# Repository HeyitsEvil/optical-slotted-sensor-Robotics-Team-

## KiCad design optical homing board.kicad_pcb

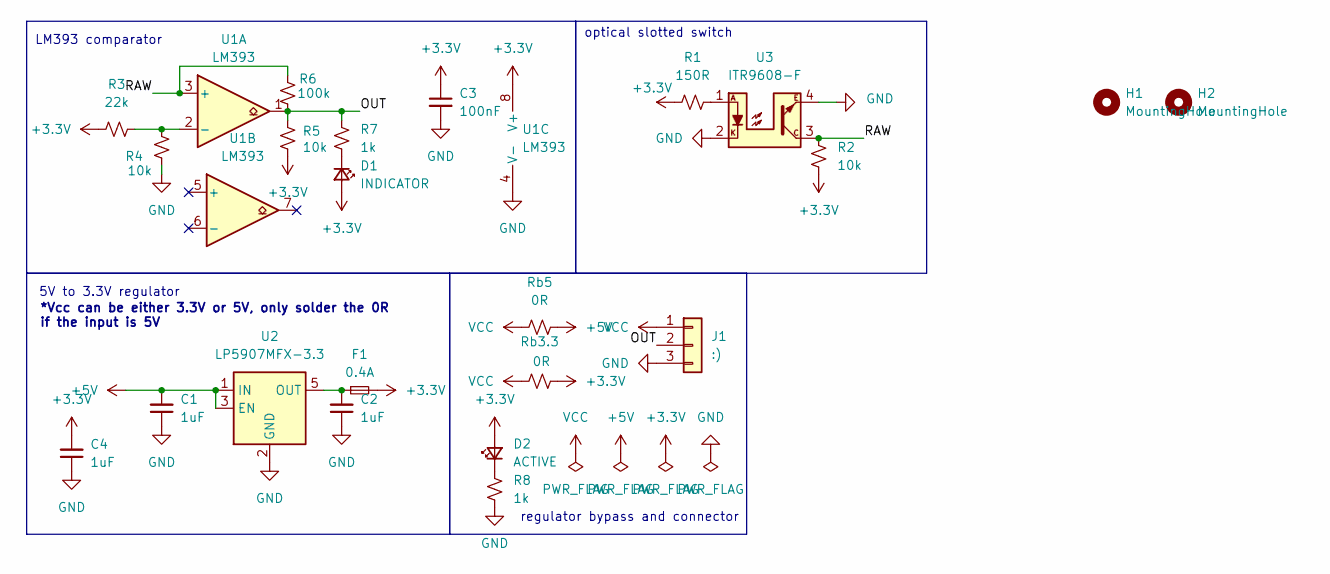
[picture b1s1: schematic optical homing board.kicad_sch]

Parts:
C1, C2, C4: 1uF; C_0603_1608Metric
C3: 100nF; C_0603_1608Metric
D1: INDICATOR; LED_0603_1608Metric
D2: ACTIVE; LED_0603_1608Metric
F1: 0.4A; R_0603_1608Metric
H1, H2: MountingHole; MountingHole_3.2mm_M3
J1: :); JST_XH_B3B-XH-A_1x03_P2.50mm_Vertical
R1: 150R; R_0603_1608Metric
R2, R4, R5: 10k; R_0603_1608Metric
R3: 22k; R_0603_1608Metric
R6: 100k; R_0603_1608Metric
R7, R8: 1k; R_0603_1608Metric
Rb3.3, Rb5: 0R; R_0603_1608Metric
U1: LM393; SOIC-8_3.9x4.9mm_P1.27mm
U2: LP5907MFX-3.3; SOT-23-5
U3: ITR9608-F; Everlight_ITR9608-F

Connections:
+3.3V: C3.1, C4.2, D1.2 (A), D2.2 (A), F1.2, R1.1, R2.2, R3.1, R5.2, Rb3.3.2, U1.8 (V+)
+5V: C1.2, Rb5.2, U2.1 (IN), U2.3 (EN)
/OUT: J1.2, R5.1, R6.2, R7.1, U1.1
/RAW: R2.1, R6.1, U1.3 (+), U3.3
GND: C1.1, C2.1, C3.2, C4.1, J1.3, R4.1, R8.2, U1.4 (V-), U2.2 (GND), U3.2, U3.4
unnamed: D1.1 (K), R7.2
unnamed: D2.1 (K), R8.1
unnamed: R1.2, U3.1
unnamed: R3.2, R4.2, U1.2 (-)
unnamed: C2.2, F1.1, U2.5 (OUT)
VCC: J1.1, Rb3.3.1, Rb5.1

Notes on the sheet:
5V to 3.3V regulator
optical slotted switch
*Vcc can be either 3.3V or 5V, only solder the 0R if the input is 5V
LM393 comparator
regulator bypass and connector

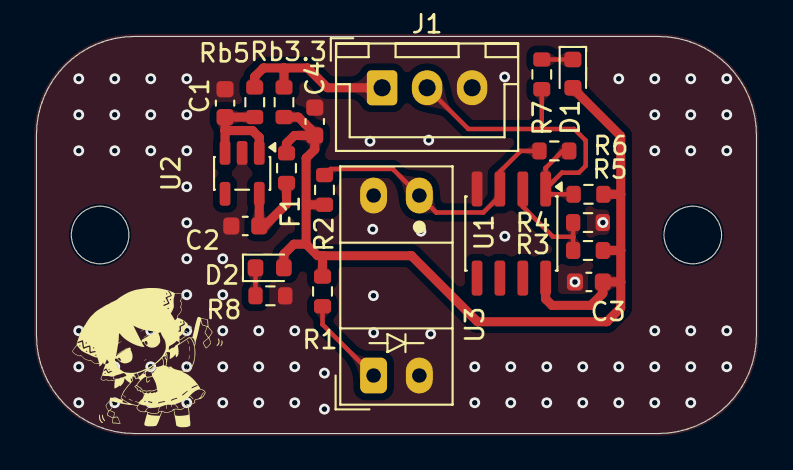
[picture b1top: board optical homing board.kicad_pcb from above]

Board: 2 copper layers, 40.0 x 22.1 mm, 23 parts (0 on the bottom side), 11 nets.
